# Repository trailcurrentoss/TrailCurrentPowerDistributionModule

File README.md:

# TrailCurrent Power Distribution Module

CAN-controlled 8-channel PWM power distribution module for vehicle lighting and accessory control with OTA firmware update capability. Part of the [TrailCurrent](https://trailcurrent.com) open-source vehicle platform.

## Hardware Overview

- **Microcontroller:** ESP32 (WROOM32)
- **Function:** 8-channel PWM lighting/accessory controller with CAN bus interface
- **Key Features:**
  - 8 independent MOSFET-driven PWM outputs (0-255 brightness)
  - CAN bus communication at 500 kbps
  - Individual and master on/off/brightness control
  - Animated light sequences (startup, interior, exterior)
  - Over-the-air (OTA) firmware updates via WiFi
  - WiFi credentials provisioned dynamically over CAN bus
  - Hierarchical PCB schematic design (5 sheets)

## Hardware Requirements

### Components

- **Microcontroller:** ESP32 development board
- **CAN Transceiver:** Vehicle CAN bus interface (TX: GPIO 15, RX: GPIO 13)
- **MOSFET Drivers:** 8 channels for PWM output switching
- **DIP Switches:** Configuration switches

### Pin Connections

**PWM Outputs:**

| GPIO | Function |
|------|----------|
| 32 | Output 1 |
| 33 | Output 2 |
| 26 | Output 3 |
| 14 | Output 4 |
| 4 | Output 5 |
| 17 | Output 6 |
| 19 | Output 7 |
| 23 | Output 8 |

### KiCAD Library Dependencies

This project uses the consolidated [TrailCurrentKiCADLibraries](https://github.com/trailcurrentoss/TrailCurrentKiCADLibraries).

**Setup:**

```bash
# Clone the library
git clone git@github.com:trailcurrentoss/TrailCurrentKiCADLibraries.git

# Set environment variables (add to ~/.bashrc or ~/.zshrc)
export TRAILCURRENT_SYMBOL_DIR="/path/to/TrailCurrentKiCADLibraries/symbols"
export TRAILCURRENT_FOOTPRINT_DIR="/path/to/TrailCurrentKiCADLibraries/footprints"
export TRAILCURRENT_3DMODEL_DIR="/path/to/TrailCurrentKiCADLibraries/3d_models"
```

See [KICAD_ENVIRONMENT_SETUP.md](https://github.com/trailcurrentoss/TrailCurrentKiCADLibraries/blob/main/docs/KICAD_ENVIRONMENT_SETUP.md) in the library repository for detailed setup instructions.

## Opening the Project

1. **Set up environment variables** (see Library Dependencies above)
2. **Open KiCAD:**
   ```bash
   kicad EDA/trailer-power-control-system.kicad_pro
   ```
3. **Verify libraries load** - All symbol and footprint libraries should resolve without errors
4. **View 3D models** - Open PCB and press `Alt+3` to view the 3D visualization

### Schematic Sheets

The design uses a hierarchical schematic with dedicated sheets:
- **Root** - Top-level connections
- **Power** - Power distribution and regulation
- **CAN** - CAN bus transceiver interface
- **MCU** - ESP32 microcontroller and support circuits
- **MOSFETs** - 8-channel MOSFET driver outputs
- **DIP Switch** - Configuration switches

## Firmware

See `src/` directory for PlatformIO-based firmware.

**Setup:**
```bash
# Install PlatformIO (if not already installed)
pip install platformio

# Build firmware
pio run

# Upload to board (serial)
pio run -t upload

# Upload via OTA (after initial flash)
pio run -t upload --upload-port esp32-DEVICE_ID
```

### Firmware Dependencies

This firmware depends on the following public libraries:

- **[OtaUpdateLibraryWROOM32](https://github.com/trailcurrentoss/OtaUpdateLibraryWROOM32)** (v0.0.1) - Over-the-air firmware update functionality
- **[TwaiTaskBasedLibraryWROOM32](https://github.com/trailcurrentoss/TwaiTaskBasedLibraryWROOM32)** (v0.0.1) - CAN bus communication interface
- **[ESP32ArduinoDebugLibrary](https://github.com/trailcurrentoss/ESP32ArduinoDebugLibrary)** (v2.0.0) - Debug macro system with compile-time removal

All dependencies are automatically resolved by PlatformIO during the build process.

### Serial Debugging

Debug output is controlled by the `DEBUG` build flag in `platformio.ini`:

```ini
build_flags = -DDEBUG=1   ; Enable debug output (default)
; build_flags = -DDEBUG=0  ; Disable — all debug calls compile away to zero overhead
```

When enabled, debug macros (`debugln()`, `debugf()`, `debug_tag()`, etc.) output to Serial at 115200 baud. When disabled (`DEBUG=0`), all debug code is completely removed at compile time with no performance or flash size impact.

**WiFi Credentials:**
- WiFi credentials are provisioned dynamically via CAN bus (Message ID 0x01)
- Credentials are stored in NVS (non-volatile storage) and persist across reboots
- For standalone testing, credentials can be set manually in firmware

### CAN Bus Protocol

**Receive (Bus to Module):**

| CAN ID | Description |
|--------|-------------|
| 0x00 | OTA update trigger (MAC-based device targeting) |
| 0x01 | WiFi credential provisioning (SSID/password via CAN) |
| 0x18 | Toggle channel on/off (byte 0 = channel 0-7, 8=all on, 9=all off) |
| 0x21 | Set brightness (byte 0 = channel, byte 1 = PWM value 0-255) |
| 0x1E | Trigger light sequence (interior/exterior animations) |

**Transmit (Module to Bus):**

| CAN ID | Description |
|--------|-------------|
| 0x1B | Status report - current PWM values for all 8 channels (8 bytes) |

## Manufacturing

- **PCB Files:** Ready for fabrication via standard PCB services (JLCPCB, OSH Park, etc.)
- **BOM Generation:** Export BOM from KiCAD schematic (Tools > Generate BOM)
- **JLCPCB Assembly:** See [BOM_ASSEMBLY_WORKFLOW.md](https://github.com/trailcurrentoss/TrailCurrentKiCADLibraries/blob/main/tools/BOM_ASSEMBLY_WORKFLOW.md) for detailed assembly workflow

## Project Structure

```
├── EDA/                          # KiCAD hardware design files
│   ├── trailer-power-control-system.kicad_pro
│   ├── trailer-power-control-system.kicad_sch  # Root schematic
│   ├── can.kicad_sch             # CAN subsystem
│   ├── mcu.kicad_sch             # MCU subsystem
│   ├── power.kicad_sch           # Power subsystem
│   ├── mosfets.kicad_sch         # 8-channel MOSFET drivers
│   ├── dip_switch.kicad_sch      # Configuration switches
│   └── trailer-power-control-system.kicad_pcb  # PCB layout
├── src/                          # Firmware source
│   ├── main.cpp                  # Main application
│   ├── globals.h                 # Pin definitions
│   ├── canHelper.h               # CAN message handling
│   ├── lightSequences.h          # Startup and animated light sequences
│   └── wifiConfig.h              # NVS WiFi credential storage
├── data/
│   └── partitions.csv            # ESP32 flash partition layout
└── platformio.ini                # Build configuration
```

## License

MIT License - See LICENSE file for details.

This is open source hardware. You are free to use, modify, and distribute these designs under the terms of the MIT license.

## Contributing

Improvements and contributions are welcome! Please submit issues or pull requests.

## Support

For questions about:
- **KiCAD setup:** See [KICAD_ENVIRONMENT_SETUP.md](https://github.com/trailcurrentoss/TrailCurrentKiCADLibraries/blob/main/docs/KICAD_ENVIRONMENT_SETUP.md)
- **Assembly workflow:** See [BOM_ASSEMBLY_WORKFLOW.md](https://github.com/trailcurrentoss/TrailCurrentKiCADLibraries/blob/main/tools/BOM_ASSEMBLY_WORKFLOW.md)

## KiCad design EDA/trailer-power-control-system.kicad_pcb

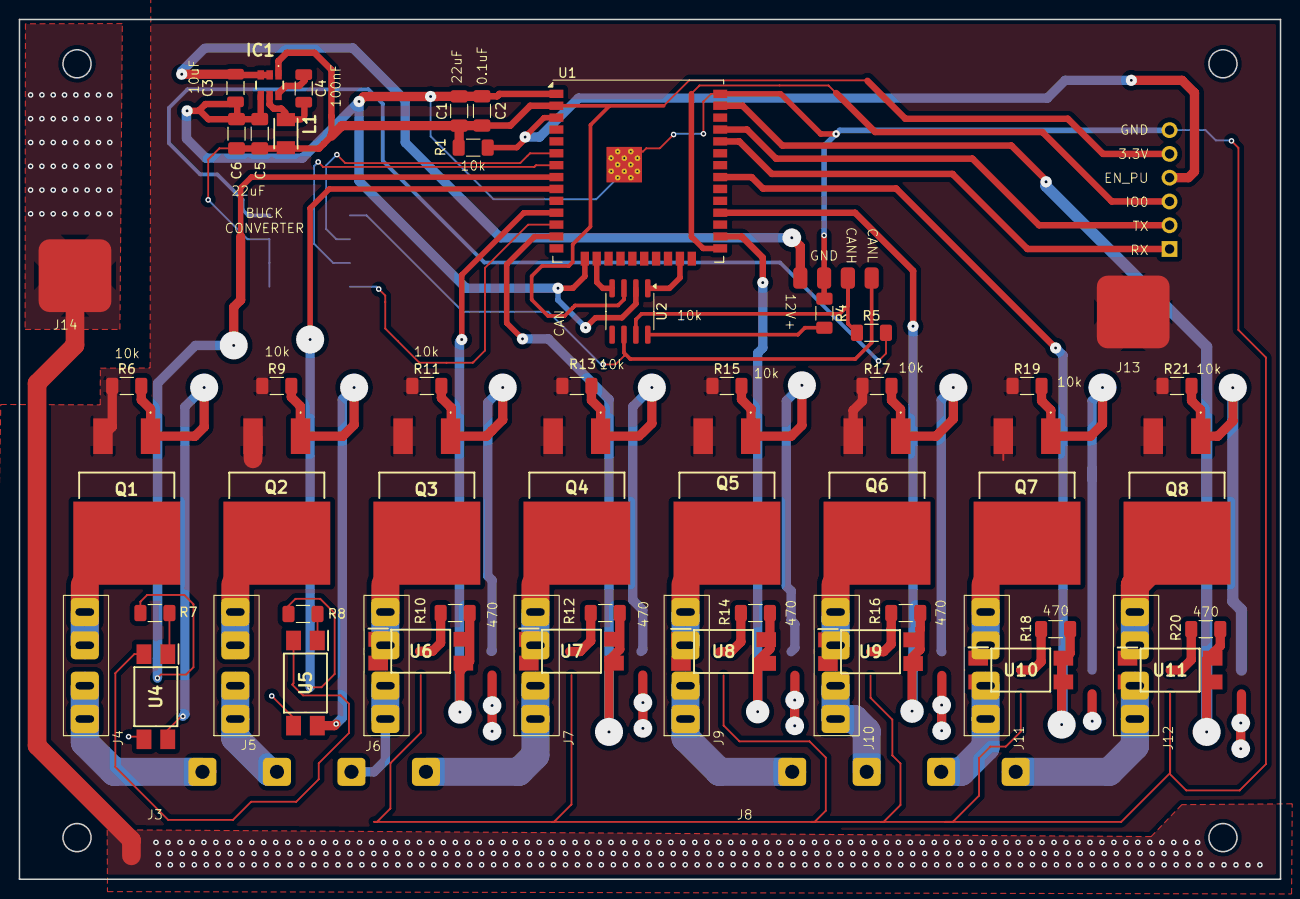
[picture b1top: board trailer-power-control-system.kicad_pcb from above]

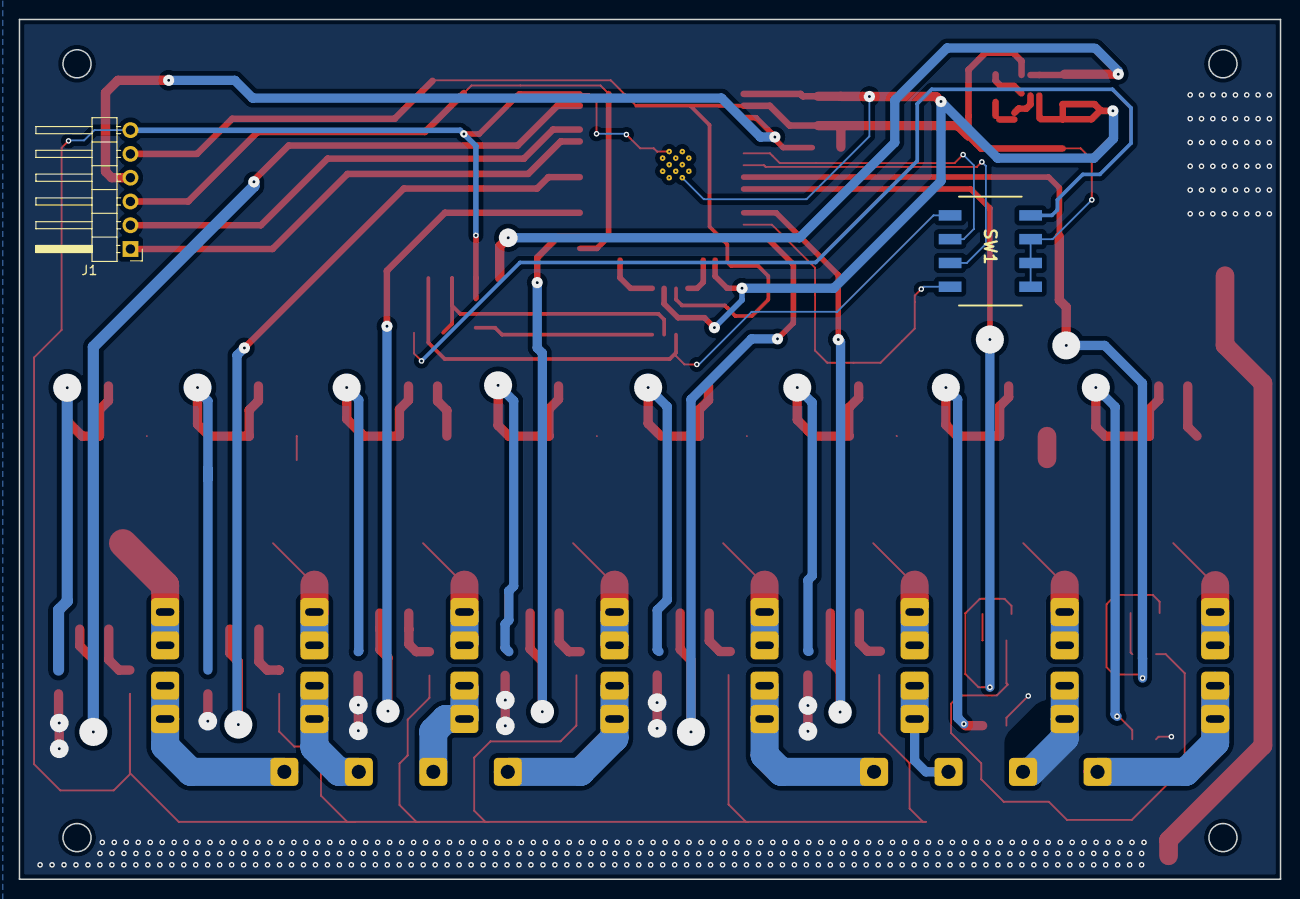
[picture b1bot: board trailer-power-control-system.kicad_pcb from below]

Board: 2 copper layers, 134.7 x 91.9 mm, 60 parts (2 on the bottom side), 60 nets.

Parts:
C1, C5, C6: 22uF; C_1206_3216Metric_Pad1.33x1.80mm_HandSolder
C2: 0.1uF; C_1206_3216Metric_Pad1.33x1.80mm_HandSolder
C3: 10uF; C_1206_3216Metric
C4: 100nF; C_1206_3216Metric
IC1: AP63203WU-7; AP63203WU7
J1: Conn_01x06; PinHeader_1x06_P2.54mm_Horizontal
J2: Conn_01x04; CAN_PLUS_POWER
J3, J8: Conn_01x04; Screw_Terminal_1x04
J4, J5, J6, J7, J9, J10, J11, J12: Conn_01x04; Automotive_Fuse_Holder
J13, J14: Conn_01x01; TestPoint_7.77mmX7.77mm
L1: NLV32T-3R9J-EF (3.9uH); NLV32T-3R9J-EF
Q1, Q2, Q3, Q4, Q5, Q6, Q7, Q8: IRF4905STRLPBF
R1, R4, R6, R9, R11, R13, R15, R17, R19, R21: 10k; R_1206_3216Metric_Pad1.30x1.75mm_HandSolder
R5: 120; R_1206_3216Metric_Pad1.30x1.75mm_HandSolder
R7, R8, R10, R12, R14, R16, R18, R20: 470; R_1206_3216Metric_Pad1.30x1.75mm_HandSolder
SW1: SW_DIP_x04; SW_DIP_219-4LPST
U1: ESP32-WROOM-32; ESP32-WROOM-32U
U2: SN65HVD230; SOIC-8_3.9x4.9mm_P1.27mm
U4, U5, U6, U7, U8, U9, U10, U11: PC817; PC817X3CSP9F

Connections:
12V_OUT01: J4.3, J4.4, Q1.2 (D)
12V_OUT02: J5.3, J5.4, Q2.2 (D)
12V_OUT03: J6.3, J6.4, Q3.2 (D)
12V_OUT04: J7.3, J7.4, Q4.2 (D)
12V_OUT05: J9.3, J9.4, Q5.2 (D)
12V_OUT06: J10.3, J10.4, Q6.2 (D)
12V_OUT07: J11.3, J11.4, Q7.2 (D)
12V_OUT08: J12.3, J12.4, Q8.2 (D)
+3.3V: C1.1, C2.1, C5.1, C6.1, IC1.1 (FB), J1.5, L1.2, R1.1, SW1.5, SW1.6, SW1.7, U1.2 (VDD), U2.3 (VCC)
+12V: C3.1, IC1.2 (EN), IC1.3 (VIN), J2.1
+15V: J13.1, Q1.3 (S), Q2.3 (S), Q3.3 (S), Q4.3 (S), Q5.3 (S), Q6.3 (S), Q7.3 (S), Q8.3 (S), R6.1, R9.1, R11.1, R13.1, R15.1, R17.1, R19.1, R21.1
CANH: J2.3, R5.1, U2.7 (CANH)
CANL: J2.4, SW1.1, U2.6 (CANL)
CAN_RX: U1.16 (IO13), U2.4 (R)
CAN_TERM_CLOSED: R5.2, SW1.8
CAN_TX: U1.23 (IO15), U2.1 (D)
DEVICE01: R7.1, U1.8 (IO32)
DEVICE02: R8.1, U1.9 (IO33)
DEVICE03: R10.1, U1.11 (IO26)
DEVICE04: R12.1, U1.13 (IO14)
DEVICE05: R14.1, U1.26 (IO4)
DEVICE06: R16.1, U1.28 (IO17)
DEVICE07: R18.1, U1.31 (IO19)
DEVICE08: R20.1, U1.37 (IO23)
DEVICE_SELECTION01: SW1.2, U1.6 (IO34)
DEVICE_SELECTION02: SW1.3, U1.7 (IO35)
DEVICE_SELECTION03: SW1.4, U1.12 (IO27)
EN: J1.4, R1.2, U1.3 (EN)
ESP32_RX: J1.1, U1.34 (RXD0/IO3)
ESP32_TX: J1.2, U1.35 (TXD0/IO1)
GND: C1.2, C2.2, C3.2, C5.2, C6.2, IC1.4 (GND), J1.6, J2.2, R4.1, U1.1 (GND), U1.15 (GND), U1.38 (GND), U1.39 (GND), U2.2 (GND), U4.2, U5.2, U6.2, U7.2, U8.2, U9.2, U10.2, U11.2
GND1: J14.1, U4.3, U5.3, U6.3, U7.3, U8.3, U9.3, U10.3, U11.3
IO0: J1.3, U1.25 (IO0)
LOAD01: J3.1, J4.1, J4.2
LOAD02: J3.2, J5.1, J5.2
LOAD03: J3.3, J6.1, J6.2
LOAD04: J3.4, J7.1, J7.2
LOAD05: J8.1, J9.1, J9.2
LOAD06: J8.2, J10.1, J10.2
LOAD07: J8.3, J11.1, J11.2
LOAD08: J8.4, J12.1, J12.2
unnamed: C4.1, IC1.6 (BST)
unnamed: C4.2, IC1.5 (SW), L1.1
unnamed: Q1.1 (G), R6.2, U4.4
unnamed: Q2.1 (G), R9.2, U5.4
unnamed: Q3.1 (G), R11.2, U6.4
unnamed: Q4.1 (G), R13.2, U7.4
unnamed: Q5.1 (G), R15.2, U8.4
unnamed: Q6.1 (G), R17.2, U9.4
unnamed: Q7.1 (G), R19.2, U10.4
unnamed: Q8.1 (G), R21.2, U11.4
unnamed: R7.2, U4.1
unnamed: R8.2, U5.1
unnamed: R10.2, U6.1
unnamed: R12.2, U7.1
unnamed: R14.2, U8.1
unnamed: R16.2, U9.1
unnamed: R18.2, U10.1
unnamed: R20.2, U11.1
unnamed: R4.2, U2.8 (Rs)

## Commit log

2026-02-12 Initial commit: Clean migration to public Codeberg repository
    This is a fresh start on Codeberg with all security and configuration
    issues addressed:
    Security fixes:
    - Removed all git history (fresh start)
    - No personal paths or credentials exposed
    - All WiFi secrets in .gitignore (using secrets.h.example pattern)
2026-02-13 Updated to align with the new approach of using the edge device to configure OTA WiFi and transmit to this devie over CAN Bus
2026-02-14 Fixing license
2026-02-14 Expand README with comprehensive project documentation
2026-02-16 Removed espota since initial firmware will be loaded via USB and subsequent will be from OTA
2026-02-16 Switched to debug library and twai with freertos task
2026-02-20 New light sequence used to validate deployment
2026-02-20 Fix for WiFi credentials over CAN
2026-02-21 Removing Jingle Bells since it was provent work
2026-02-22 Bringing CAD model back in
2026-02-23 Logo added to case and work started to update the EDA
2026-02-23 Add trailcurrent.com link to README
2026-02-25 Fixed paths to KiCAD components
2026-03-01 Added logo to cover with correct orientation for printing
